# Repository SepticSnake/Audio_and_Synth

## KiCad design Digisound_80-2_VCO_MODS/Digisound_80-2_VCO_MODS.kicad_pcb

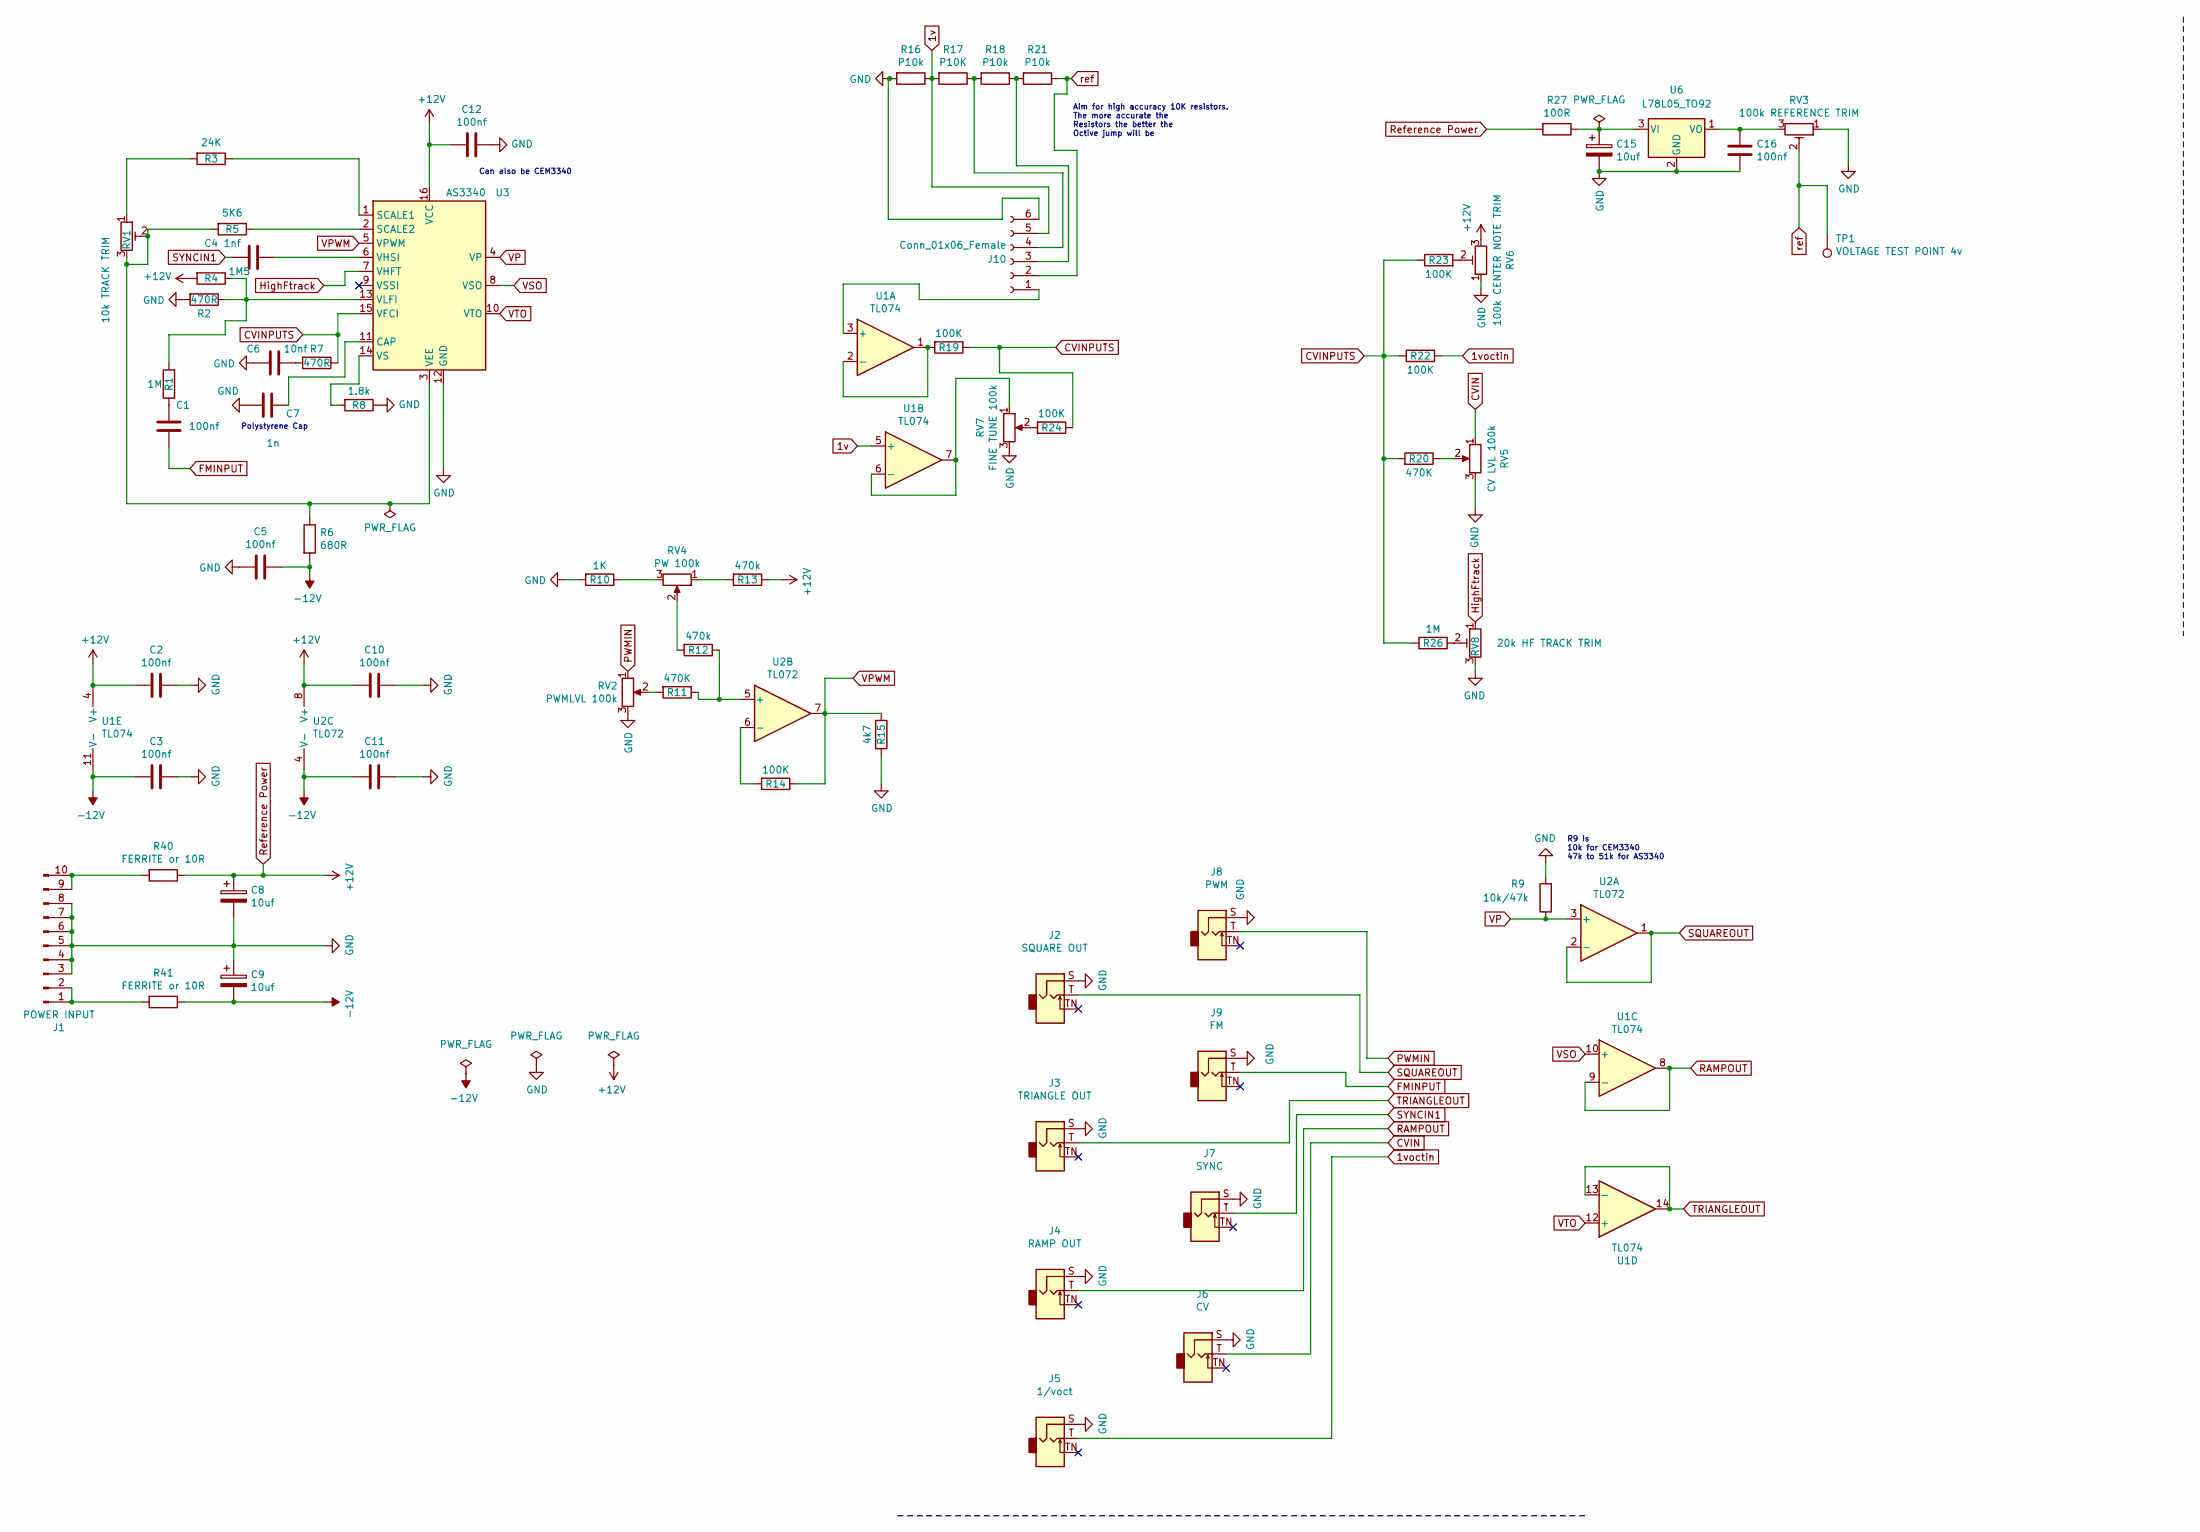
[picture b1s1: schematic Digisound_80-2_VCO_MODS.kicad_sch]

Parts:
C1, C2, C3, C5, C10, C11, C12, C16: 100nf; C_Disc_D5.0mm_W2.5mm_P5.00mm
C4: 1nf; C_Disc_D5.0mm_W2.5mm_P5.00mm
C6: 10nf; C_Disc_D5.0mm_W2.5mm_P5.00mm
C7: 1n; C_Disc_D5.0mm_W2.5mm_P5.00mm
C8, C9, C15: 10uf; CP_Radial_D4.0mm_P2.00mm
J1: POWER INPUT; IDC-Header_2x05_P2.54mm_Vertical
J2: SQUARE OUT; Jack_3.5mm_QingPu_WQP-PJ398SM_Vertical_CircularHoles
J3: TRIANGLE OUT; Jack_3.5mm_QingPu_WQP-PJ398SM_Vertical_CircularHoles
J4: RAMP OUT; Jack_3.5mm_QingPu_WQP-PJ398SM_Vertical_CircularHoles
J5: 1/voct; Jack_3.5mm_QingPu_WQP-PJ398SM_Vertical_CircularHoles
J6: CV; Jack_3.5mm_QingPu_WQP-PJ398SM_Vertical_CircularHoles
J7: SYNC; Jack_3.5mm_QingPu_WQP-PJ398SM_Vertical_CircularHoles
J8: PWM; Jack_3.5mm_QingPu_WQP-PJ398SM_Vertical_CircularHoles
J9: FM; Jack_3.5mm_QingPu_WQP-PJ398SM_Vertical_CircularHoles
J10: Conn_01x06_Female; PinHeader_1x06_P2.54mm_Vertical
R1, R26: 1M; R_Axial_DIN0207_L6.3mm_D2.5mm_P2.54mm_Vertical
R2, R7: 470R; R_Axial_DIN0207_L6.3mm_D2.5mm_P2.54mm_Vertical
R3: 24K; R_Axial_DIN0207_L6.3mm_D2.5mm_P2.54mm_Vertical
R4: 1M5; R_Axial_DIN0207_L6.3mm_D2.5mm_P2.54mm_Vertical
R5: 5K6; R_Axial_DIN0207_L6.3mm_D2.5mm_P2.54mm_Vertical
R6: 680R; R_Axial_DIN0207_L6.3mm_D2.5mm_P2.54mm_Vertical
R8: 1.8k; R_Axial_DIN0207_L6.3mm_D2.5mm_P2.54mm_Vertical
R9: 10k/47k; R_Axial_DIN0207_L6.3mm_D2.5mm_P2.54mm_Vertical
R10: 1K; R_Axial_DIN0207_L6.3mm_D2.5mm_P2.54mm_Vertical
R11, R20: 470K; R_Axial_DIN0207_L6.3mm_D2.5mm_P2.54mm_Vertical
R12, R13: 470k; R_Axial_DIN0207_L6.3mm_D2.5mm_P2.54mm_Vertical
R14, R19, R22, R23, R24: 100K; R_Axial_DIN0207_L6.3mm_D2.5mm_P2.54mm_Vertical
R15: 4k7; R_Axial_DIN0207_L6.3mm_D2.5mm_P2.54mm_Vertical
R16, R18, R21: P10k; R_Axial_DIN0207_L6.3mm_D2.5mm_P2.54mm_Vertical
R17: P10K; R_Axial_DIN0207_L6.3mm_D2.5mm_P2.54mm_Vertical
R27: 100R; R_Axial_DIN0207_L6.3mm_D2.5mm_P2.54mm_Vertical
R40, R41: FERRITE or 10R; R_Axial_DIN0207_L6.3mm_D2.5mm_P7.62mm_Horizontal
RV1: 10k TRACK TRIM; Potentiometer_Bourns_3296W_Vertical
RV2: PWMLVL 100k; Potentiometer_Alpha_RD901F-40-00D_Single_Vertical
RV3: 100k REFERENCE TRIM; Potentiometer_Bourns_3296W_Vertical
RV4: PW 100k; Potentiometer_Alpha_RD901F-40-00D_Single_Vertical
RV5: CV LVL 100k; Potentiometer_Alpha_RD901F-40-00D_Single_Vertical
RV6: 100k CENTER NOTE TRIM; Potentiometer_Bourns_3296W_Vertical
RV7: FINE TUNE 100k; Potentiometer_Alpha_RD901F-40-00D_Single_Vertical
RV8: 20k HF TRACK TRIM; Potentiometer_Bourns_3296W_Vertical
TP1: VOLTAGE TEST POINT 4v; TestPoint_THTPad_D2.0mm_Drill1.0mm
U1: TL074; DIP-14_W7.62mm_Socket_LongPads
U2: TL072; DIP-8_W7.62mm_Socket_LongPads
U3: AS3340; DIP-16_W7.62mm_Socket_LongPads
U6: L78L05_TO92; TO-92_Inline

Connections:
1v: J10.5, R16.1, R17.2, U1.5 (+)
1voctin: J5.T, R22.2
-12V: C3.2, C5.1, C9.2, C11.2, R6.2, R41.1, U1.11 (V-), U2.4 (V-)
CVIN: J6.T, RV5.1
CVINPUTS: R7.1, R19.1, R20.2, R22.1, R23.1, R24.1, R26.1, U3.15 (VFCI)
FMINPUT: C1.1, J9.T
GND: C2.1, C3.1, C5.2, C6.2, C7.2, C8.2, C9.1, C10.1, C11.1, C12.1, C15.2, C16.2, J1.3, J1.4, J1.5, J1.6, J1.7, J1.8, J2.S, J3.S, J4.S, J5.S, J6.S, J7.S, J8.S, J9.S, J10.6, R2.2, R8.1, R9.2, R10.2, R15.2, R16.2, RV2.3, RV3.1, RV5.3, RV6.1, RV7.3, RV8.3, U3.12 (GND), U6.2 (GND)
HighFtrack: RV8.1, U3.7 (VHFT)
unnamed: C1.2, R1.1
unnamed: C6.1, R7.2
unnamed: J1.1, J1.2, R41.2
unnamed: J1.9, J1.10, R40.2
unnamed: J10.1, U1.3 (+)
unnamed: J10.3, R18.1, R21.2
unnamed: J10.4, R17.1, R18.2
unnamed: R3.2, RV1.1
unnamed: R10.1, RV4.3
unnamed: R11.2, RV2.2
unnamed: R12.2, RV4.2
unnamed: R13.2, RV4.1
unnamed: R20.1, RV5.2
unnamed: R23.2, RV6.2
unnamed: R24.2, RV7.2
unnamed: R26.2, RV8.2
unnamed: R19.2, U1.1, U1.2 (-)
unnamed: RV7.1, U1.6 (-), U1.7
unnamed: R11.1, R12.1, U2.5 (+)
unnamed: R14.2, U2.6 (-)
unnamed: C7.1, U3.11 (CAP)
unnamed: R3.1, U3.1 (SCALE1)
unnamed: R5.1, U3.2 (SCALE2)
unnamed: R5.2, R6.1, RV1.2, RV1.3, U3.3 (VEE)
unnamed: C4.1, U3.6 (VHSI)
unnamed: R1.2, R2.1, R4.1, U3.13 (VLFI)
unnamed: R8.2, U3.14 (VS)
unnamed: C15.1, R27.1, U6.3 (VI)
unnamed: C16.1, RV3.3, U6.1 (VO)
PWMIN: J8.T, RV2.1
RAMPOUT: J4.T, U1.8, U1.9 (-)
Reference Power: C2.2, C8.1, C10.2, C12.2, R4.2, R13.1, R27.2, R40.1, RV6.3, U1.4 (V+), U2.8 (V+), U3.16 (VCC)
SQUAREOUT: J2.T, U2.1, U2.2 (-)
SYNCIN1: C4.2, J7.T
TRIANGLEOUT: J3.T, U1.13 (-), U1.14
VP: R9.1, U2.3 (+), U3.4 (VP)
VPWM: R14.1, R15.1, U2.7, U3.5 (VPWM)
VSO: U1.10 (+), U3.8 (VSO)
VTO: U1.12 (+), U3.10 (VTO)
ref: J10.2, R21.1, RV3.2, TP1.1 (1_1)

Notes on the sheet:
Polystyrene Cap
R9 is 10k for CEM3340 47k to 51k for AS3340
Aim for high accuracy 10K resistors. The more accurate the Resistors the better the Octive jump will be
Can also be CEM3340

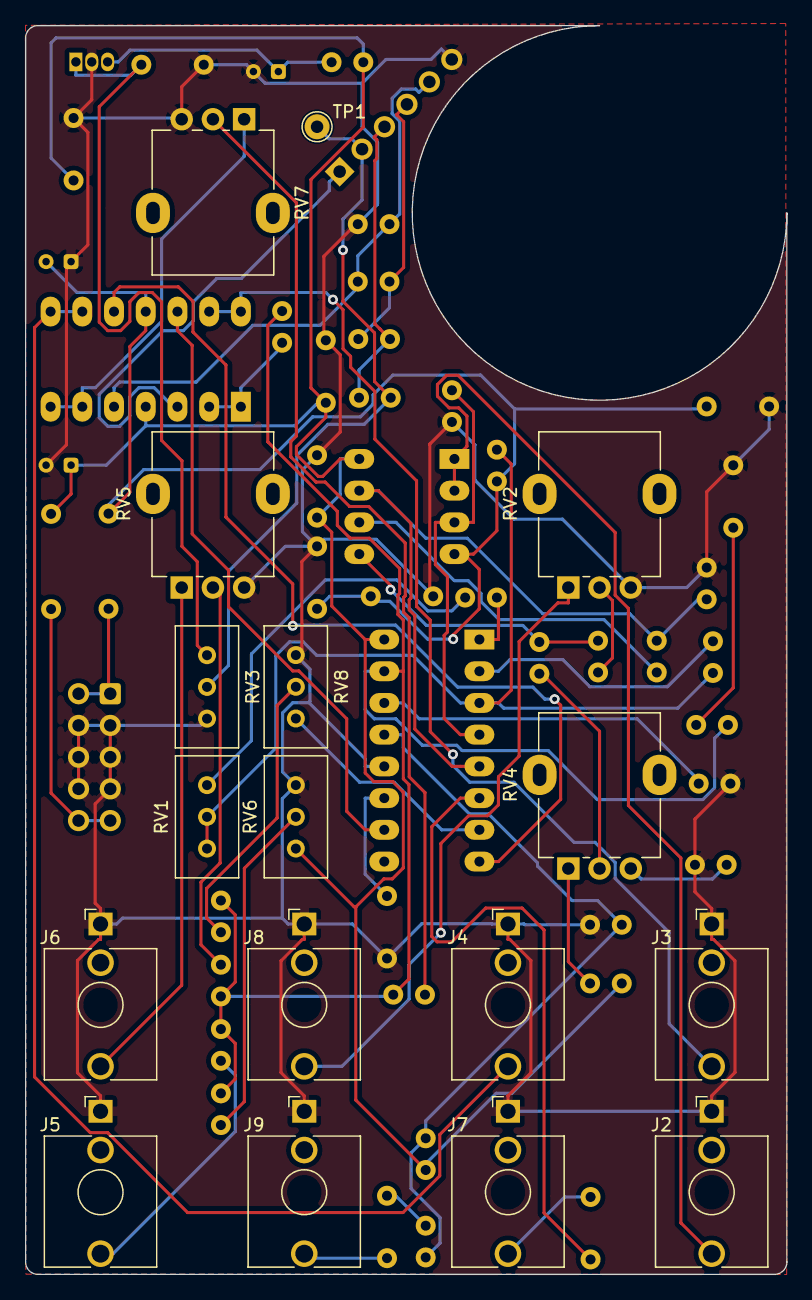
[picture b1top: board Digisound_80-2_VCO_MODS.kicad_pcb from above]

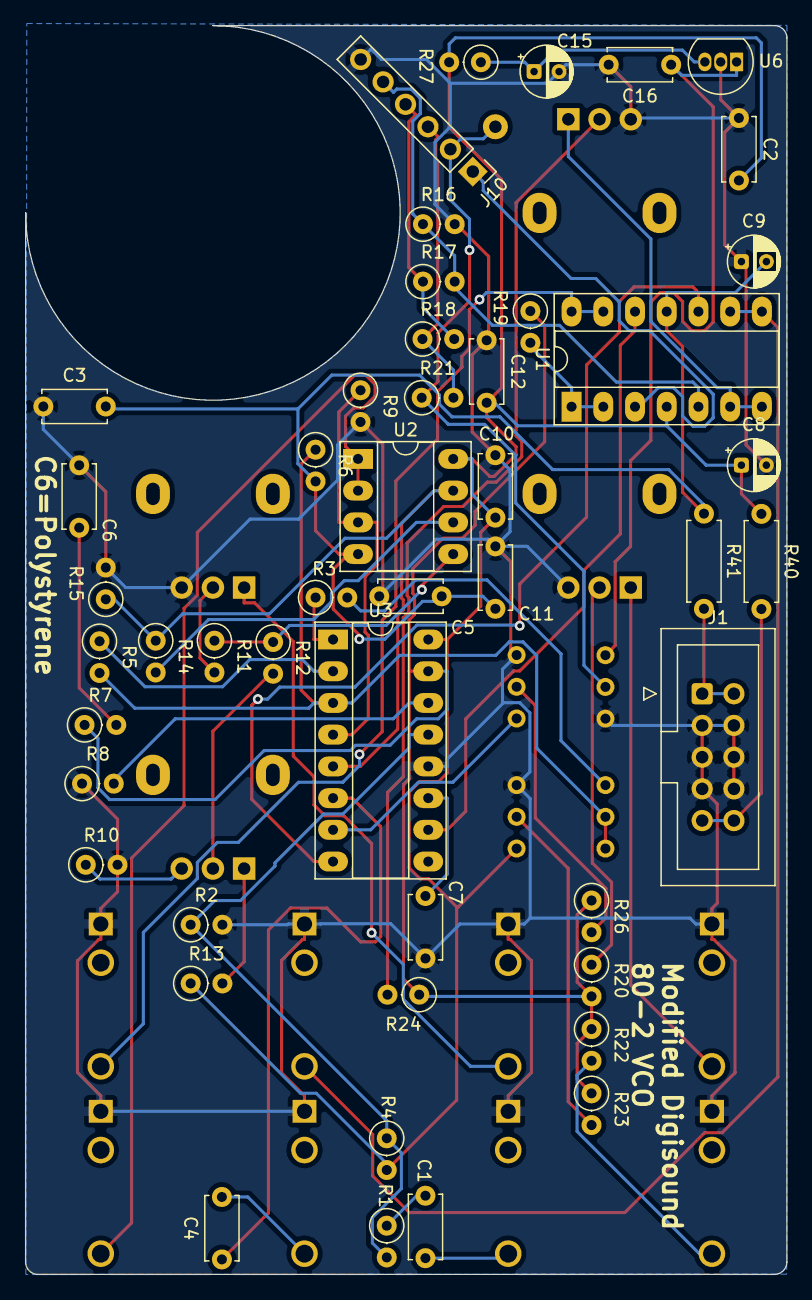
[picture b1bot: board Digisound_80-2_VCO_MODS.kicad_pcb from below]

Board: 2 copper layers, 61.0 x 100.0 mm, 65 parts (48 on the bottom side), 48 nets.

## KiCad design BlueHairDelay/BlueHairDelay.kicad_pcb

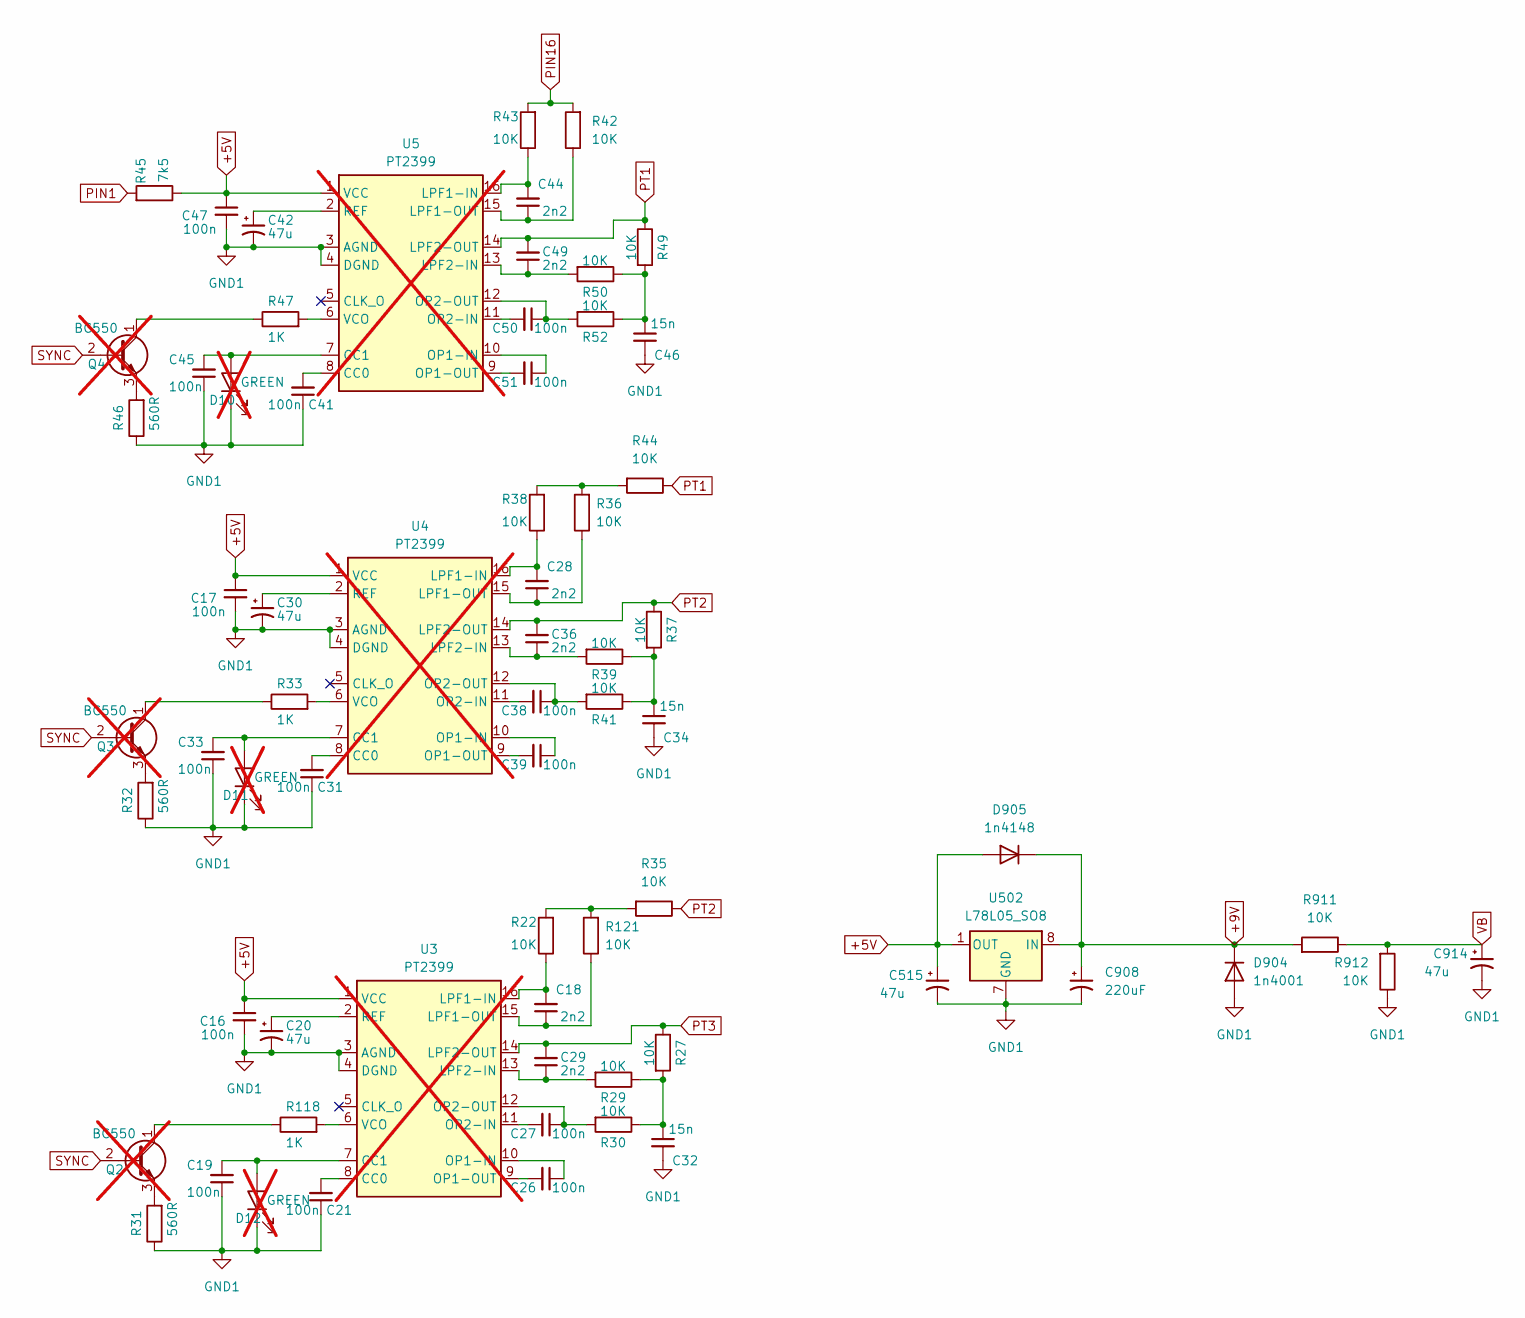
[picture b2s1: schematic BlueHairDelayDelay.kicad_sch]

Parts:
C16, C17, C19, C21, C26, C27, C31, C33, C38, C39, C41, C45, C47, C50, C51: 100n; C_0805_2012Metric
C18, C28, C29, C36, C44, C49: 2n2; C_0805_2012Metric
C20, C30, C42, C515, C914: 47u; CP_Elec_5x5.4
C32, C34, C46: 15n; C_0805_2012Metric
C908: 220uF; CP_Elec_6.3x5.4
D10, D11, D12: GREEN; LED_D3.0mm; not fitted
D904: 1n4001; Package_DO-214AC
D905: 1n4148; D_SOD-123F
Q2, Q3, Q4: BC550; TO-92_Inline; not fitted
R22, R27, R29, R30, R35, R36, R37, R38, R39, R41, R42, R43, R44, R49, R50, R52, R121, R911, R912: 10K; R_0805_2012Metric
R31, R32, R46: 560R; R_0805_2012Metric
R33, R47, R118: 1K; R_0805_2012Metric
R45: 7k5; R_0805_2012Metric
U3, U4, U5: PT2399; DIP-16_W7.62mm; not fitted
U502: L78L05_SO8; SOIC-8_3.9x4.9mm_P1.27mm

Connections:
+5V: C16.1, C17.1, C47.1, C515.1, D905.2 (A), R45.1, U3.1 (VCC), U4.1 (VCC), U5.1 (VCC), U502.1 (OUT)
+9V: C908.1, D904.1 (K), D905.1 (K), R911.2, U502.8 (IN); also elsewhere on the board
unnamed: C32.1, R27.2, R29.1, R30.1
unnamed: C34.1, R37.2, R39.1, R41.1
unnamed: C46.1, R49.2, R50.1, R52.1
unnamed: C45.2, D10.2 (A), U5.7 (CC1)
unnamed: C33.2, D11.2 (A), U4.7 (CC1)
unnamed: C19.2, D12.2 (A), U3.7 (CC1)
unnamed: Q2.1 (C), R118.1
unnamed: Q2.3 (E), R31.2
unnamed: Q3.1 (C), R33.1
unnamed: Q3.3 (E), R32.2
unnamed: Q4.1 (C), R47.1
unnamed: Q4.3 (E), R46.2
unnamed: R36.2, R38.2, R44.2
unnamed: R22.2, R35.2, R121.2
unnamed: C21.2, U3.8 (CC0)
unnamed: C18.2, R22.1, U3.16 (LPF1-IN)
unnamed: C18.1, R121.1, U3.15 (LPF1-OUT)
unnamed: C29.1, R29.2, U3.13 (LPF2-IN)
unnamed: C26.1, U3.10 (OP1-IN)
unnamed: C26.2, U3.9 (OP1-OUT)
unnamed: C27.2, U3.11 (OP2-IN)
unnamed: C27.1, R30.2, U3.12 (OP2-OUT)
unnamed: C20.1, U3.2 (REF)
unnamed: R118.2, U3.6 (VCO)
unnamed: C31.2, U4.8 (CC0)
unnamed: C28.2, R38.1, U4.16 (LPF1-IN)
unnamed: C28.1, R36.1, U4.15 (LPF1-OUT)
unnamed: C36.1, R39.2, U4.13 (LPF2-IN)
unnamed: C39.1, U4.10 (OP1-IN)
unnamed: C39.2, U4.9 (OP1-OUT)
unnamed: C38.2, U4.11 (OP2-IN)
unnamed: C38.1, R41.2, U4.12 (OP2-OUT)
unnamed: C30.1, U4.2 (REF)
unnamed: R33.2, U4.6 (VCO)
unnamed: C41.2, U5.8 (CC0)
unnamed: C44.2, R43.1, U5.16 (LPF1-IN)
unnamed: C44.1, R42.1, U5.15 (LPF1-OUT)
unnamed: C49.1, R50.2, U5.13 (LPF2-IN)
unnamed: C51.1, U5.10 (OP1-IN)
unnamed: C51.2, U5.9 (OP1-OUT)
unnamed: C50.2, U5.11 (OP2-IN)
unnamed: C50.1, R52.2, U5.12 (OP2-OUT)
unnamed: C42.1, U5.2 (REF)
unnamed: R47.2, U5.6 (VCO)
PIN1: R45.2; also elsewhere on the board
PIN16: R42.2, R43.2; also elsewhere on the board
PT1: C49.2, R44.1, R49.1, U5.14 (LPF2-OUT); also elsewhere on the board
PT2: C36.2, R35.1, R37.1, U4.14 (LPF2-OUT); also elsewhere on the board
PT3: C29.2, R27.1, U3.14 (LPF2-OUT); also elsewhere on the board
SYNC: Q2.2 (B), Q3.2 (B), Q4.2 (B); also elsewhere on the board
TAILS3: C16.2, C17.2, C19.1, C20.2, C21.1, C30.2, C31.1, C32.2, C33.1, C34.2, C41.1, C42.2, C45.1, C46.2, C47.2, C515.2, C908.2, C914.2, D10.1 (K), D11.1 (K), D12.1 (K), D904.2 (A), R31.1, R32.1, R46.1, R912.1, U3.3 (AGND), U3.4 (DGND), U4.3 (AGND), U4.4 (DGND), U5.3 (AGND), U5.4 (DGND), U502.2 (GND), U502.3 (GND), U502.6 (GND), U502.7 (GND); also elsewhere on the board
VB: C914.1, R911.1, R912.2; also elsewhere on the board

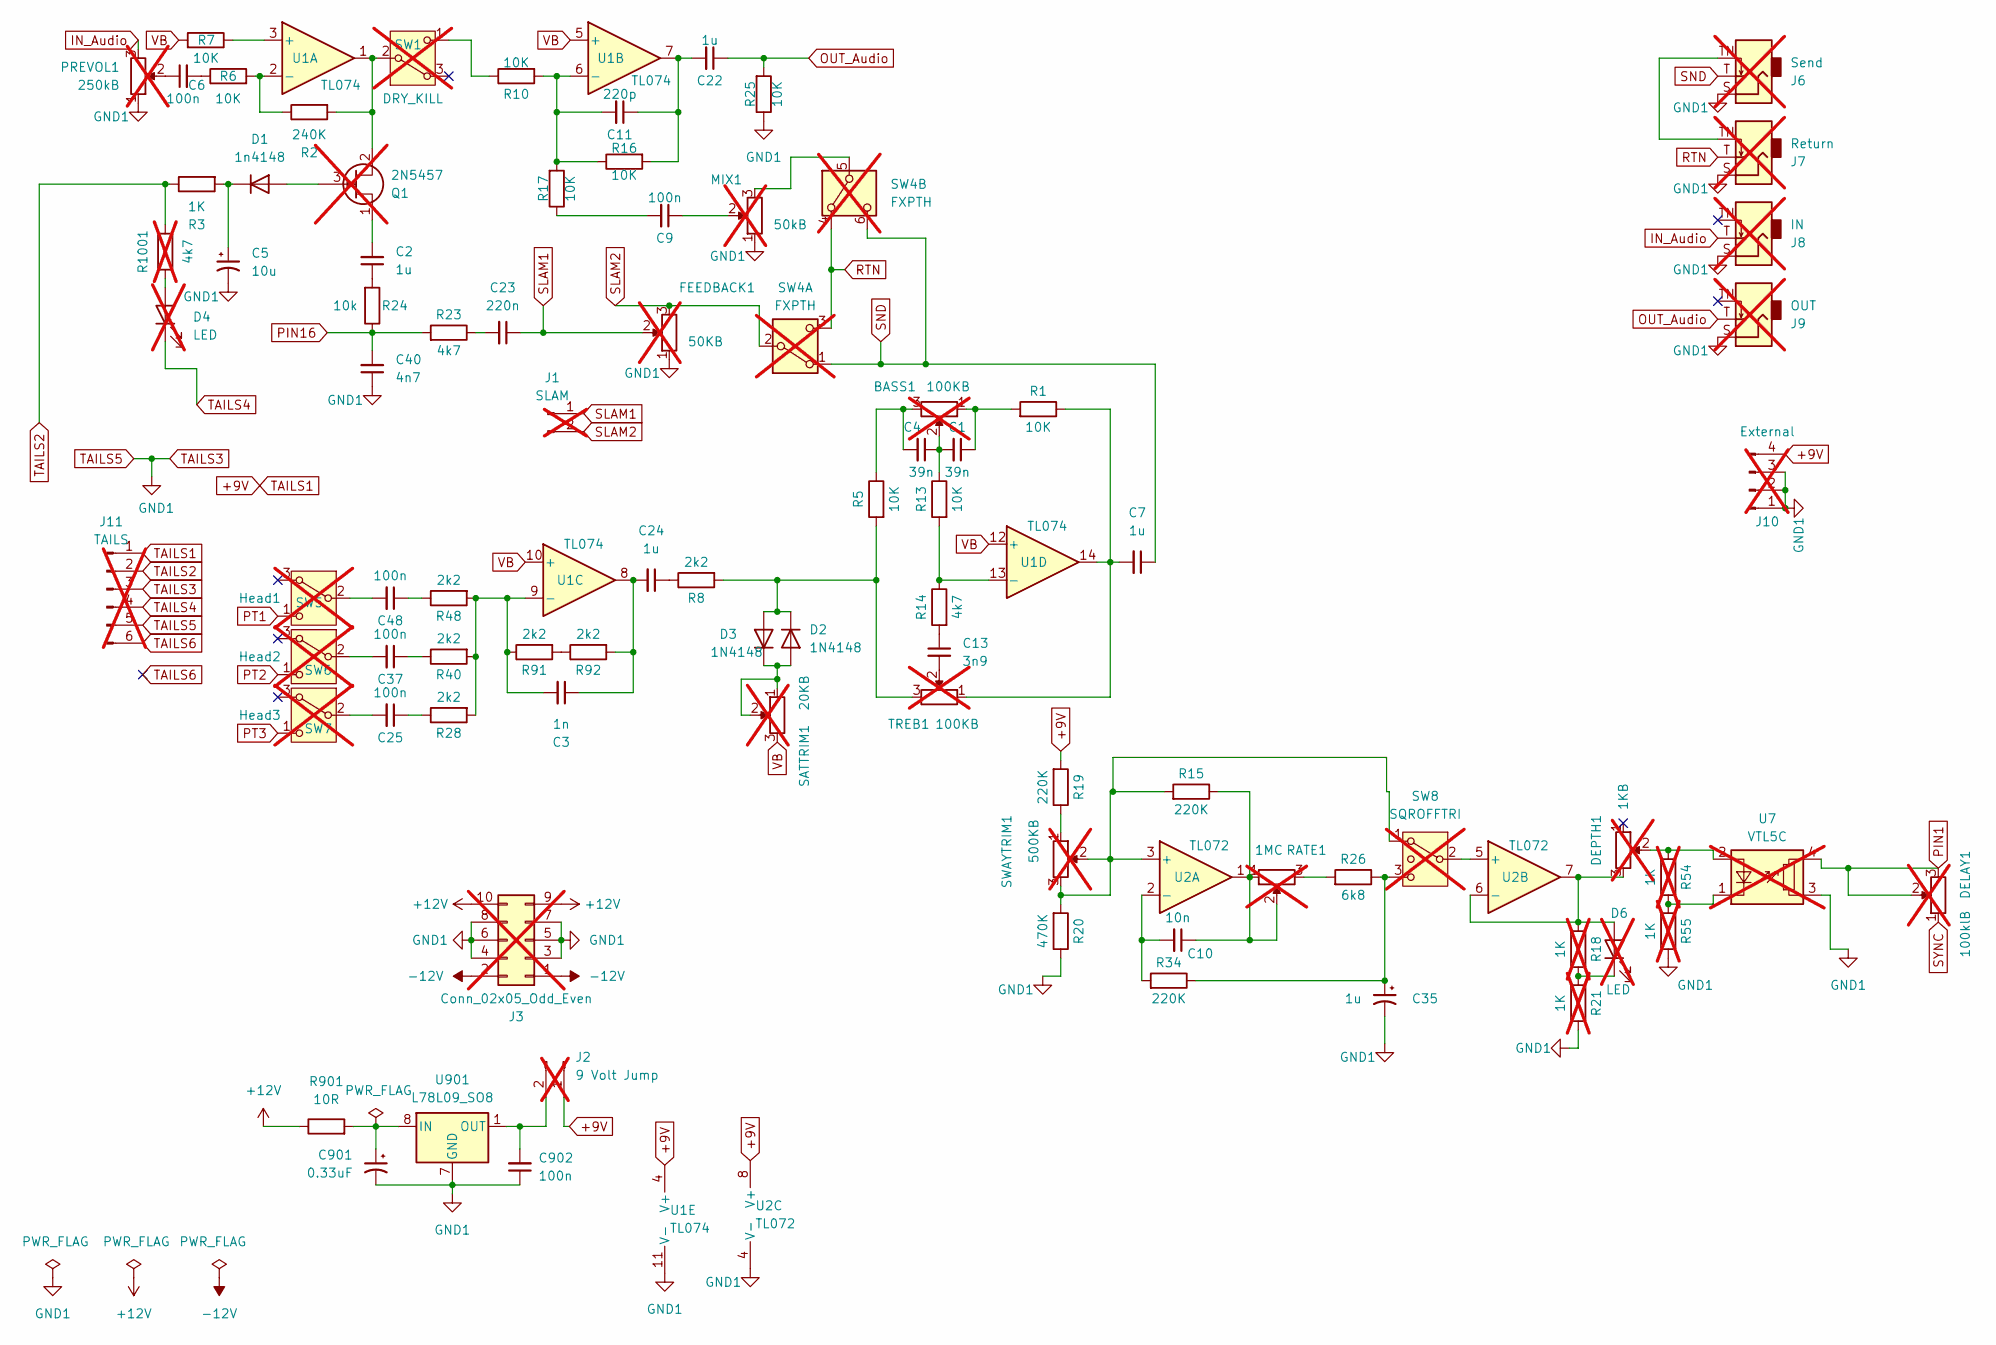
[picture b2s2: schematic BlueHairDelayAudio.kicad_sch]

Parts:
BASS1: 100KB; Potentiometer_Alpha_RD901F-40-00D_Single_Vertical; not fitted
C1, C4: 39n; C_0805_2012Metric
C2, C7, C22, C24: 1u; C_0805_2012Metric
C3: 1n; C_0805_2012Metric
C5: 10u; CP_Elec_4x5.4
C6, C9, C25, C37, C48, C902: 100n; C_0805_2012Metric
C10: 10n; C_0805_2012Metric
C11: 220p; C_0805_2012Metric
C13: 3n9; C_0805_2012Metric
C23: 220n; C_0805_2012Metric
C35: 1u; CP_Elec_4x5.4
C40: 4n7; C_0805_2012Metric
C901: 0.33uF; CP_Elec_4x5.4
D1: 1n4148; D_SOD-123F
D2, D3: 1N4148; D_SOD-123F
D4, D6: LED; LED_D3.0mm; not fitted
DELAY1: 100klB; Potentiometer_Alpha_RD901F-40-00D_Single_Vertical; not fitted
DEPTH1: 1KB; Potentiometer_Alpha_RD901F-40-00D_Single_Vertical; not fitted
FEEDBACK1: 50KB; Potentiometer_Alpha_RD901F-40-00D_Single_Vertical; not fitted
J1: SLAM; PinHeader_1x02_P2.54mm_Vertical; not fitted
J2: 9 Volt Jump; PinHeader_1x02_P2.54mm_Vertical; not fitted
J3: Conn_02x05_Odd_Even; IDC-Header_2x05_P2.54mm_Vertical; not fitted
J6: Send; Jack_3.5mm_QingPu_WQP-PJ398SM_Vertical_CircularHoles; not fitted
J7: Return; Jack_3.5mm_QingPu_WQP-PJ398SM_Vertical_CircularHoles; not fitted
J8: IN; Jack_3.5mm_QingPu_WQP-PJ398SM_Vertical_CircularHoles; not fitted
J9: OUT; Jack_3.5mm_QingPu_WQP-PJ398SM_Vertical_CircularHoles; not fitted
J10: External; PinHeader_1x04_P2.54mm_Vertical; not fitted
J11: TAILS; PinHeader_1x06_P2.54mm_Vertical; not fitted
MIX1: 50kB; Potentiometer_Alpha_RD901F-40-00D_Single_Vertical; not fitted
PREVOL1: 250kB; Potentiometer_Alpha_RD901F-40-00D_Single_Vertical; not fitted
Q1: 2N5457; TO-92; not fitted
R1, R5, R6, R7, R10, R13, R16, R17, R25: 10K; R_0805_2012Metric
R2: 240K; R_0805_2012Metric
R3: 1K; R_0805_2012Metric
R8, R28, R40, R48, R91, R92: 2k2; R_0805_2012Metric
R14, R23: 4k7; R_0805_2012Metric
R15, R19, R34: 220K; R_0805_2012Metric
R18, R21, R54, R55: 1K; R_Axial_DIN0207_L6.3mm_D2.5mm_P2.54mm_Vertical; not fitted
R20: 470K; R_0805_2012Metric
R24: 10k; R_0805_2012Metric
R26: 6k8; R_0805_2012Metric
R901: 10R; R_0805_2012Metric
R1001: 4k7; R_Axial_DIN0207_L6.3mm_D2.5mm_P2.54mm_Vertical; not fitted
RATE1: 1MC; Potentiometer_Alpha_RD901F-40-00D_Single_Vertical; not fitted
SATTRIM1: 20KB; Potentiometer_Runtron_RM-065_Vertical; not fitted
SW1: DRY_KILL; Switch_Toggle_1P2T_LongSlots; not fitted
SW4: FXPTH; SW_SubMicro_2P2T_Toggle_LongSlots; not fitted
SW5: Head1; Switch_Toggle_1P2T_LongSlots; not fitted
SW6: Head2; Switch_Toggle_1P2T_LongSlots; not fitted
SW7: Head3; Switch_Toggle_1P2T_LongSlots; not fitted
SW8: SQROFFTRI; Switch_Toggle_1P2T_LongSlots; not fitted
SWAYTRIM1: 500KB; Potentiometer_Runtron_RM-065_Vertical; not fitted
TREB1: 100KB; Potentiometer_Alpha_RD901F-40-00D_Single_Vertical; not fitted
U1: TL074; SO-14_3.9x8.65mm_P1.27mm
U2: TL072; SO-8_3.9x4.9mm_P1.27mm
U7: VTL5C; PerkinElmer_VTL5C; not fitted
U901: L78L09_SO8; SOIC-8_3.9x4.9mm_P1.27mm

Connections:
+9V: J2.1, J10.4, J11.1, R19.2, U1.4 (V+), U2.8 (V+); also elsewhere on the board
+12V: J3.9, J3.10, R901.1
-12V: J3.1, J3.2
IN_Audio: J8.T, PREVOL1.3
unnamed: BASS1.1, C1.1, R1.2
unnamed: BASS1.2, C1.2, C4.1, R13.1
unnamed: BASS1.3, C4.2, R5.1
unnamed: C2.1, R24.2
unnamed: C6.1, PREVOL1.2
unnamed: C6.2, R6.1
unnamed: C7.2, R1.1, TREB1.1, U1.14
unnamed: C9.1, MIX1.2
unnamed: C9.2, R17.1
unnamed: C10.1, R15.1, RATE1.1, RATE1.2, U2.1
unnamed: C11.1, C22.2, R16.2, U1.7
unnamed: C13.1, R14.2
unnamed: C13.2, TREB1.2
unnamed: C23.2, R23.1
unnamed: C24.1, R8.1
unnamed: C3.1, C24.2, R92.2, U1.8
unnamed: C25.1, R28.1
unnamed: C37.1, R40.1
unnamed: C48.1, R48.1
unnamed: D1.2 (A), Q1.3 (G)
unnamed: C5.1, D1.1 (K), R3.2
unnamed: D2.2 (A), D3.1 (K), SATTRIM1.1, SATTRIM1.2
unnamed: D2.1 (K), D3.2 (A), R5.2, R8.2, TREB1.3
unnamed: D4.2 (A), R1001.1
unnamed: D6.2 (A), DEPTH1.3, R18.2, U2.6 (-), U2.7
unnamed: D6.1 (K), R18.1, R21.2
unnamed: C902.2, J2.2, U901.1 (OUT)
unnamed: J6.TN, J7.TN
unnamed: C2.2, Q1.1 (D)
unnamed: Q1.2 (S), R2.2, SW1.2 (B), U1.1
unnamed: R19.1, SWAYTRIM1.1
unnamed: R26.2, RATE1.3
unnamed: R91.2, R92.1
unnamed: R10.1, SW1.1 (C)
unnamed: MIX1.3, SW4.5 (B)
unnamed: C48.2, SW5.2 (B)
unnamed: C37.2, SW6.2 (B)
unnamed: C25.2, SW7.2 (B)
unnamed: SW8.2 (3), U2.5 (+)
unnamed: C35.1, R26.1, R34.1, SW8.3 (4)
unnamed: R7.1, U1.3 (+)
unnamed: R2.1, R6.2, U1.2 (-)
unnamed: C11.2, R10.2, R16.1, R17.2, U1.6 (-)
unnamed: C3.2, R28.2, R40.2, R48.2, R91.1, U1.9 (-)
unnamed: R13.2, R14.1, U1.13 (-)
unnamed: R15.2, R20.2, SW8.1, SWAYTRIM1.2, SWAYTRIM1.3, U2.3 (+)
unnamed: C10.2, R34.2, U2.2 (-)
unnamed: DEPTH1.2, R54.2, U7.2 (+)
unnamed: R54.1, R55.2, U7.1 (-)
unnamed: C901.1, R901.2, U901.8 (IN)
OUT_Audio: C22.1, J9.T, R25.2
PIN1: DELAY1.2, DELAY1.3, U7.4; also elsewhere on the board
PIN16: C40.2, R23.2, R24.1; also elsewhere on the board
PT1: SW5.1 (C); also elsewhere on the board
PT2: SW6.1 (C); also elsewhere on the board
PT3: SW7.1 (C); also elsewhere on the board
RTN: J7.T, SW4.3 (C), SW4.4 (A)
SLAM1: C23.1, FEEDBACK1.2, J1.1
SLAM2: FEEDBACK1.3, J1.2, SW4.2 (B)
SND: C7.1, J6.T, SW4.1 (A), SW4.6 (C)
SYNC: DELAY1.1; also elsewhere on the board
TAILS2: J11.2, R3.1, R1001.2
TAILS3: C5.2, C35.2, C40.1, C901.2, C902.1, FEEDBACK1.1, J3.3, J3.4, J3.5, J3.6, J3.7, J3.8, J6.S, J7.S, J8.S, J9.S, J10.1, J10.2, J10.3, J11.3, J11.5, MIX1.1, PREVOL1.1, R20.1, R21.1, R25.1, R55.1, U1.11 (V-), U2.4 (V-), U7.3, U901.2 (GND), U901.3 (GND), U901.6 (GND), U901.7 (GND); also elsewhere on the board
TAILS4: D4.1 (K), J11.4
TAILS6: J11.6
VB: R7.2, SATTRIM1.3, U1.5 (+), U1.10 (+), U1.12 (+); also elsewhere on the board

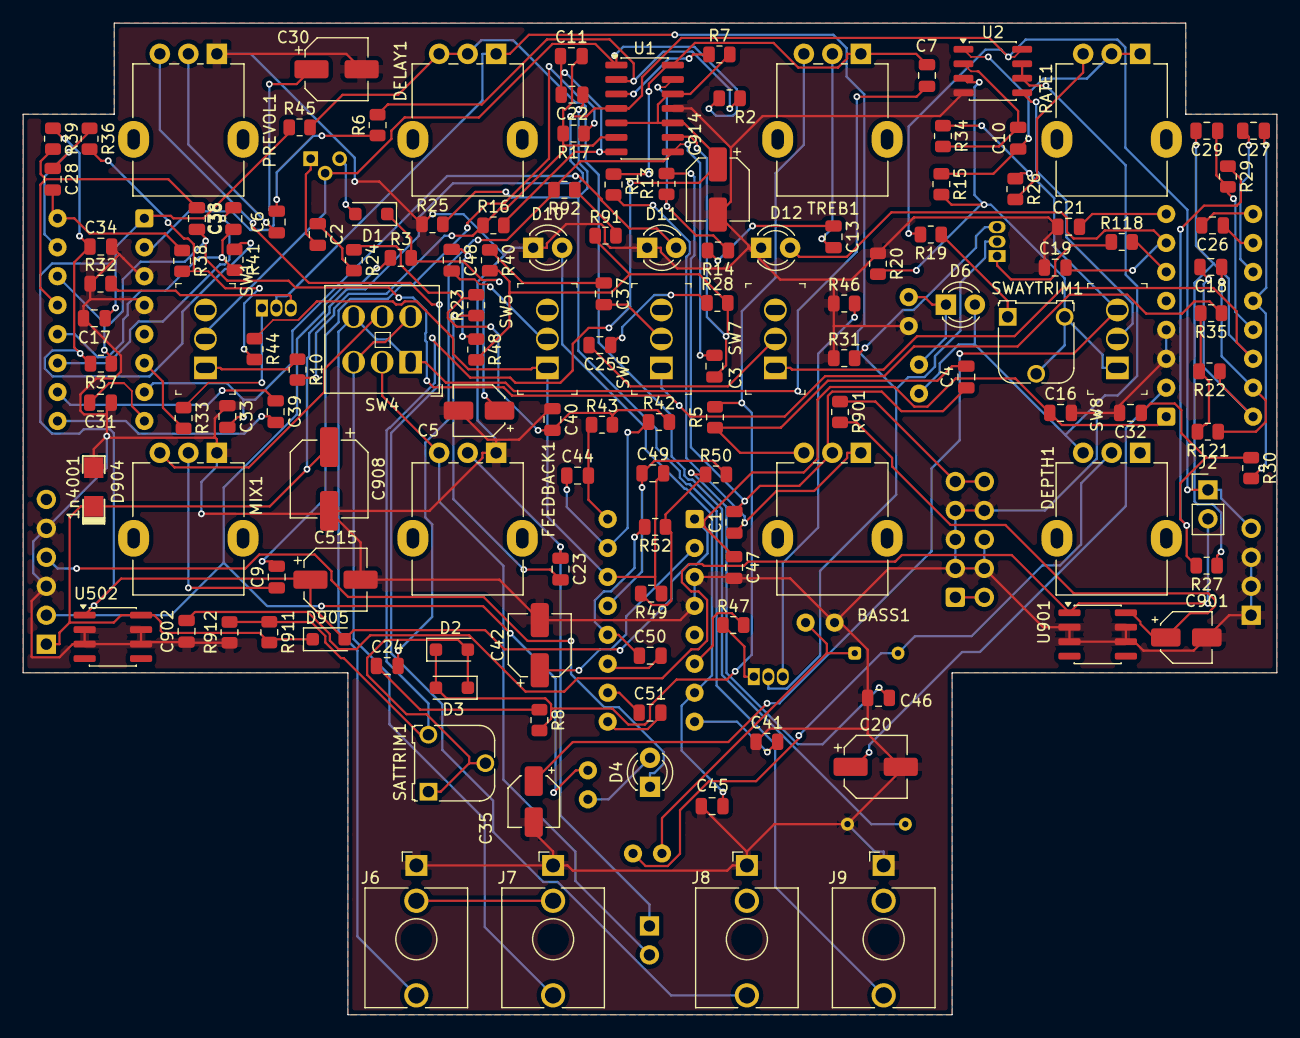
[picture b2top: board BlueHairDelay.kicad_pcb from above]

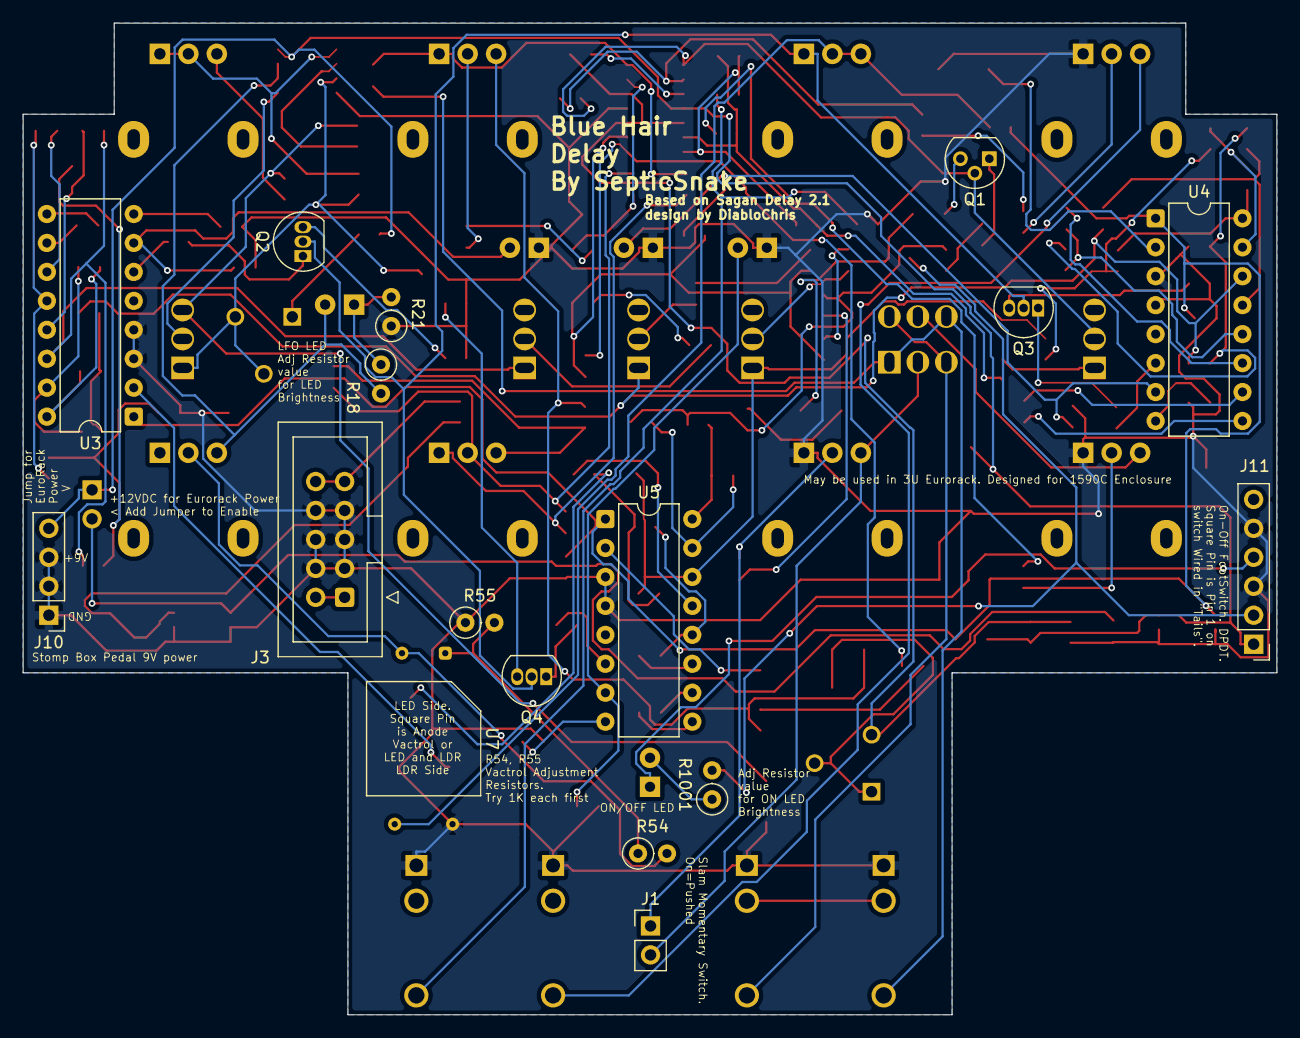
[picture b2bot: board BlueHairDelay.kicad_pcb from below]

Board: 2 copper layers, 110.0 x 87.0 mm, 155 parts (17 on the bottom side), 114 nets.

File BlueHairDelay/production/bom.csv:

Designator,Footprint,Quantity,Value,LCSC Part #
"C1, C4",0805,2,39n,
C10,0805,1,10n,
C11,0805,1,220p,
C13,0805,1,3n9,
"C16, C17, C19, C21, C25, C26, C27, C31, C33, C37, C38, C39, C41, C45, C47, C48, C50, C51, C6, C9, C902",0805,21,100n,
"C18, C28, C29, C36, C44, C49",0805,6,2n2,
"C2, C22, C24, C7",0805,4,1u,
"C20, C30, C42, C515, C914",CP_Elec_5x5.4,5,47u,
C23,0805,1,220n,
C3,0805,1,1n,
"C32, C34, C46",0805,3,15n,
C35,CP_Elec_4x5.4,1,1u,
C40,0805,1,4n7,
C5,CP_Elec_4x5.4,1,10u,
C901,CP_Elec_4x5.4,1,0.33uF,
C908,CP_Elec_6.3x5.4,1,220uF,
"D1, D2, D3, D905",D_SOD-123F,4,1n4148,
D904,Package_DO-214AC,1,1n4001,
J1,PinHeader_1x02_P2.54mm_Vertical,1,SLAM,
J10,PinHeader_1x04_P2.54mm_Vertical,1,External,
J2,PinHeader_1x02_P2.54mm_Vertical,1,9 Volt Jump,
J6,Jack_3.5mm_QingPu_WQP-PJ398SM_Vertical_CircularHoles,1,Send,
J7,Jack_3.5mm_QingPu_WQP-PJ398SM_Vertical_CircularHoles,1,Return,
J8,Jack_3.5mm_QingPu_WQP-PJ398SM_Vertical_CircularHoles,1,IN,
J9,Jack_3.5mm_QingPu_WQP-PJ398SM_Vertical_CircularHoles,1,OUT,
"R1, R10, R121, R13, R16, R17, R22, R24, R25, R27, R29, R30, R35, R36, R37, R38, R39, R41, R42, R43, R44, R49, R5, R50, R52, R6, R7, R911, R912",0805,29,10K,
"R118, R3, R33, R47",0805,4,1K,
"R14, R23",0805,2,4k7,
"R15, R19, R34",0805,3,220K,
R2,0805,1,240K,
R20,0805,1,470K,
R26,0805,1,6k8,
"R28, R40, R48, R8, R91, R92",0805,6,2k2,
"R31, R32, R46",0805,3,560R,
R45,0805,1,7k5,
R901,0805,1,10R,
U1,SO-14_3.9x8.65mm_P1.27mm,1,TL074,
U2,SO-8_3.9x4.9mm_P1.27mm,1,TL072,
U502,SOIC-8_3.9x4.9mm_P1.27mm,1,L78L05_SO8,
U901,SOIC-8_3.9x4.9mm_P1.27mm,1,L78L09_SO8,
